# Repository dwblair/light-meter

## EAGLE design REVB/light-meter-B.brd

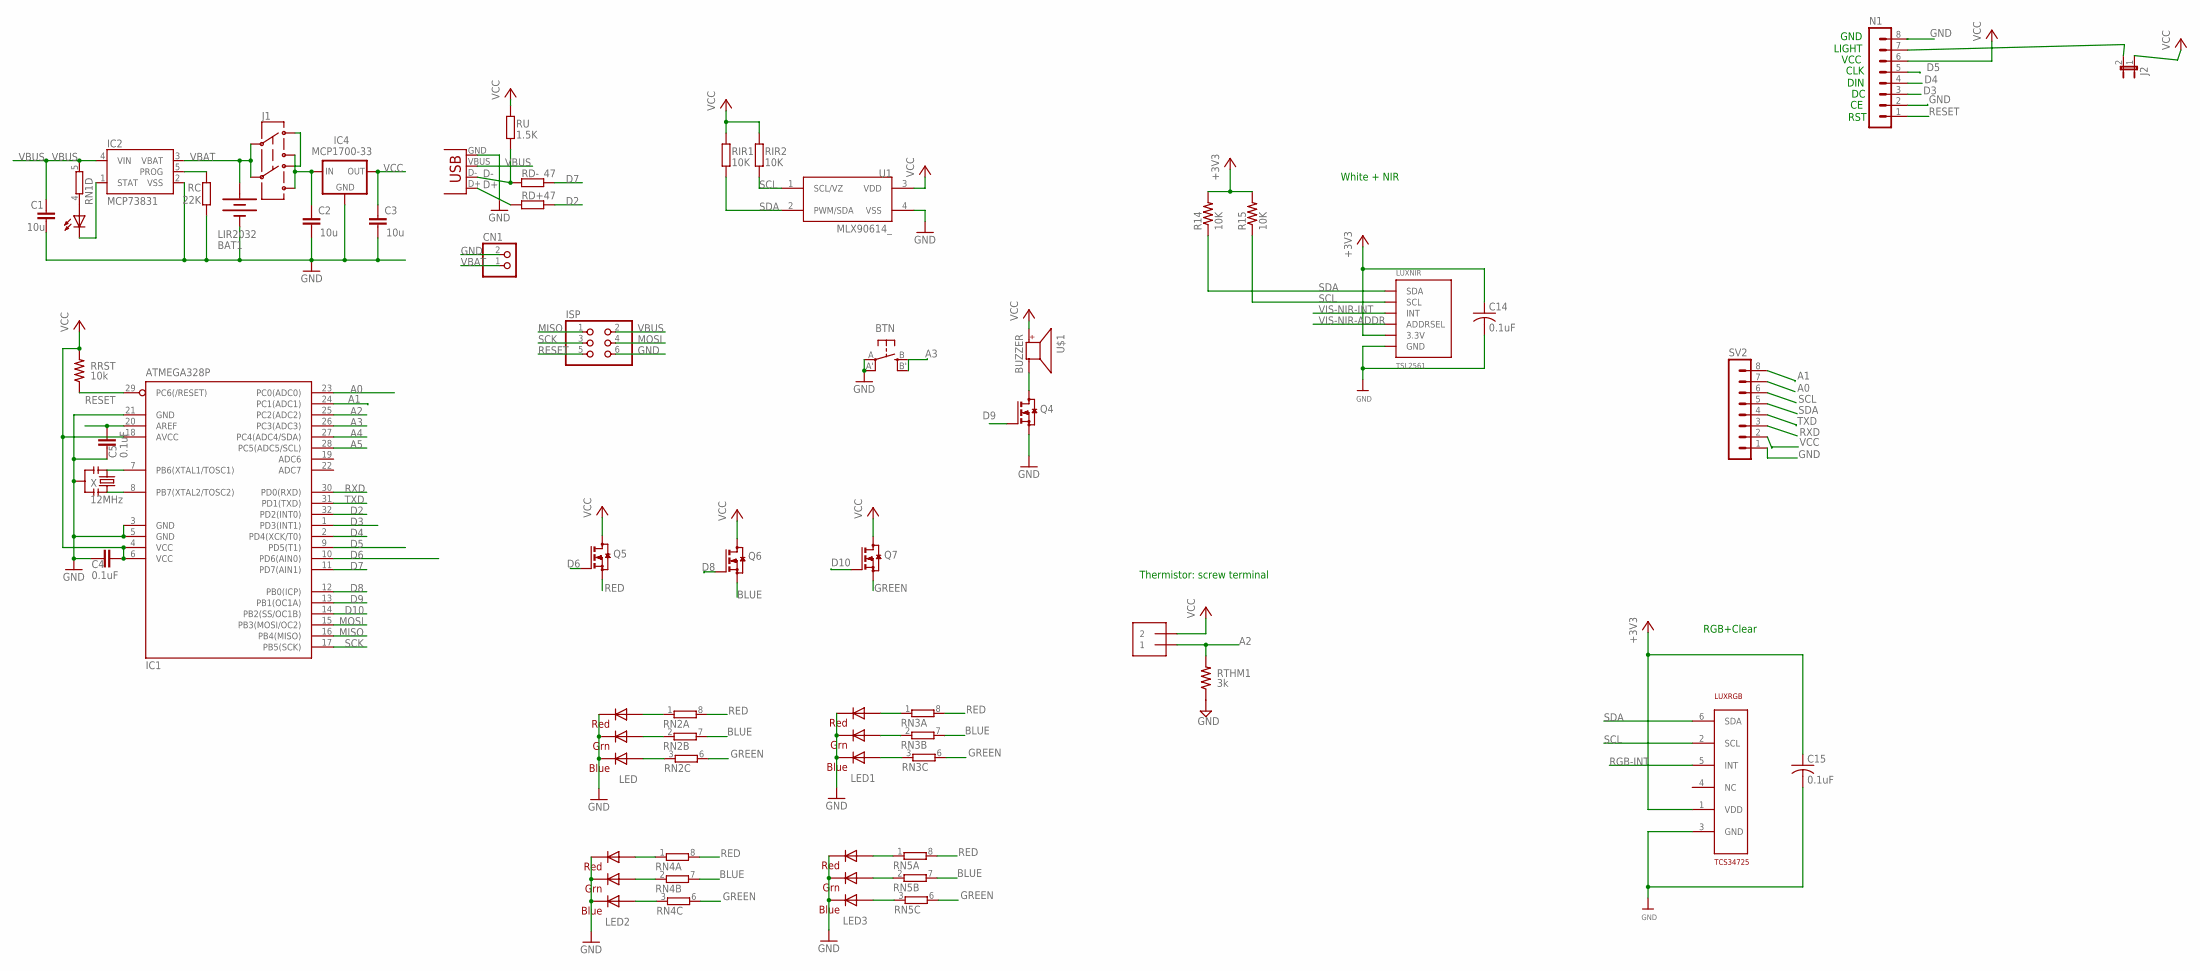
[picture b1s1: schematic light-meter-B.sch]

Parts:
BAT1: LIR2032; BATTCOM_20MM_PTH_SMT
BTN: EVQQ2; EVQ-Q2
C1, C2, C3: 10u; C0805
C4, C5, C14, C15: 0.1uF; C0805
CHG: 0805; CHIPLED_0805
CN1: JST_2PIN-SMT-RA; JST-PH-2-SMT-RA
IC1: ATMEGA328P; TQFP32-08
IC2: MCP73831; SOT23-5
IC4: MCP1700-33; SOT23
ISP: PINHD-2X3; 2X03
J1: AYZ0202
J2: JP1E; JP1
LED, LED1, LED2, LED3: RGBLED5050
LUXNIR: TSL2561; TSL2561_FN@1
LUXRGB: TCS34725; DFN-6
N1: MA08-1
Q4, Q5, Q6, Q7: BSS123; SOT23
R14, R15: 10K; R0805
RC: 22K; R0805
RD+: 47; R0805
RD-: 47; R0805
RIR1, RIR2: 10K; R0805
RN1, RN2, RN3, RN4, RN5: 4R-NEXB38V; EXB38V
RRST: 10k; R0805@1
RTHM1: 3k; R0805@1
RU: 1.5K; R0805
SV2: MA08-1
THM1: 1X2-3.5MM
U1: MLX90614_; TO-39
U$1: BUZZER; SMT-8585-BUZZER
X: 12MHz; RESONATOR-SMD
X1: USBSMD; USB-MINIB

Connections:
+3V3: C14.1, C15.1, LUXNIR.VDD (3.3V), LUXRGB.1 (VDD), R14.2, R15.2
A0: IC1.23 (PC0(ADC0)), SV2.7
A1: IC1.24 (PC1(ADC1)), SV2.8
A2: IC1.25 (PC2(ADC2)), RTHM1.2, THM1.1
A3: BTN.B (S), BTN.B' (S1), IC1.26 (PC3(ADC3))
A4: IC1.27 (PC4(ADC4/SDA))
A5: IC1.28 (PC5(ADC5/SCL))
AREF: C5.2, IC1.20 (AREF)
BLUE: Q6.2 (S), RN2.7 (2), RN3.7 (2), RN4.7 (2), RN5.7 (2)
D2: IC1.32 (PD2(INT0)), RD+.2
D3: IC1.1 (PD3(INT1)), N1.3
D4: IC1.2 (PD4(XCK/T0)), N1.4
D5: IC1.9 (PD5(T1)), N1.5
D6: IC1.10 (PD6(AIN0)), Q5.1 (G)
D7: IC1.11 (PD7(AIN1)), RD-.2
D8: IC1.12 (PB0(ICP)), Q6.1 (G)
D9: IC1.13 (PB1(OC1A)), Q4.1 (G)
D10: IC1.14 (PB2(SS/OC1B)), Q7.1 (G)
D+: RD+.1, X1.D+
D-: RD-.1, RU.1, X1.D-
GND: BAT1.P$1 (-), BTN.A, BTN.A' (P1), C1.2, C2.2, C3.2, C4.1, C5.1, C14.2, C15.2, CN1.2 (1), IC1.3 (GND), IC1.5 (GND), IC1.21 (GND), IC2.2 (VSS), IC4.1 (GND), ISP.6, LED.4 (BLUE_C), LED.5 (RED_C), LED.6 (GREEN_C), LED1.4 (BLUE_C), LED1.5 (RED_C), LED1.6 (GREEN_C), LED2.4 (BLUE_C), LED2.5 (RED_C), LED2.6 (GREEN_C), LED3.4 (BLUE_C), LED3.5 (RED_C), LED3.6 (GREEN_C), LUXNIR.VSS (GND), LUXRGB.3 (GND), N1.2, N1.8, Q4.2 (S), RC.1, RTHM1.1, SV2.1, U1.4 (VSS), X.2, X1.GND
GREEN: Q7.2 (S), RN2.6 (2), RN3.6 (2), RN4.6 (2), RN5.6 (2)
MISO: IC1.16 (PB4(MISO)), ISP.1
MOSI: IC1.15 (PB3(MOSI/OC2)), ISP.4
unnamed: J1.3 (1), J1.6 (4)
unnamed: IC1.7 (PB6(XTAL1/TOSC1)), X.1
unnamed: IC1.8 (PB7(XTAL2/TOSC2)), X.3
unnamed: LED.3 (BLUE_A), RN2.3 (1)
unnamed: CHG.C, IC2.1 (STAT)
unnamed: IC2.5 (PROG), RC.2
unnamed: Q4.3 (D), U$1.-
unnamed: J2.2, N1.7
unnamed: LED.1 (GREEN_A), RN2.2 (1)
unnamed: CHG.A, RN1.4 (1)
unnamed: LED.2 (RED_A), RN2.1
unnamed: LED1.3 (BLUE_A), RN3.3 (1)
unnamed: LED1.1 (GREEN_A), RN3.2 (1)
unnamed: LED1.2 (RED_A), RN3.1
unnamed: LED2.3 (BLUE_A), RN4.3 (1)
unnamed: LED2.1 (GREEN_A), RN4.2 (1)
unnamed: LED2.2 (RED_A), RN4.1
unnamed: LED3.3 (BLUE_A), RN5.3 (1)
unnamed: LED3.1 (GREEN_A), RN5.2 (1)
unnamed: LED3.2 (RED_A), RN5.1
RED: Q5.2 (S), RN2.8 (2), RN3.8 (2), RN4.8 (2), RN5.8 (2)
RESET: IC1.29 (PC6(/RESET)), ISP.5, N1.1, RRST.1
RGB-INT: LUXRGB.5 (INT)
RXD: IC1.30 (PD0(RXD)), SV2.3
SCK: IC1.17 (PB5(SCK)), ISP.3
SCL: LUXNIR.CLK (SCL), LUXRGB.2 (SCL), R15.1, RIR2.1, SV2.6, U1.1 (SCL/VZ)
SDA: LUXNIR.DATA (SDA), LUXRGB.6 (SDA), R14.1, RIR1.1, SV2.5, U1.2 (PWM/SDA)
TXD: IC1.31 (PD1(TXD)), SV2.4
VBAT: BAT1.P$2 (+), CN1.1 (2), IC2.3 (VBAT), J1.2, J1.5
VBUS: C1.1, IC2.4 (VIN), ISP.2, RN1.5 (2), X1.VBUS
VCC: C3.1, C4.2, IC1.4 (VCC), IC1.6 (VCC), IC1.18 (AVCC), IC4.2 (OUT), J2.1, N1.6, Q5.3 (D), Q6.3 (D), Q7.3 (D), RIR1.2, RIR2.2, RRST.2, RU.2, SV2.2, THM1.2, U1.3 (VDD), U$1.+
VDD: C2.1, IC4.3 (IN), J1.1 (3), J1.4 (6)
VIS-NIR-ADDR: LUXNIR.ADR (ADDRSEL)
VIS-NIR-INT: LUXNIR.INT

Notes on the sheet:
RGB+Clear
White + NIR
RST
DIN
CLK
VCC
LIGHT
GND
Thermistor: screw terminal

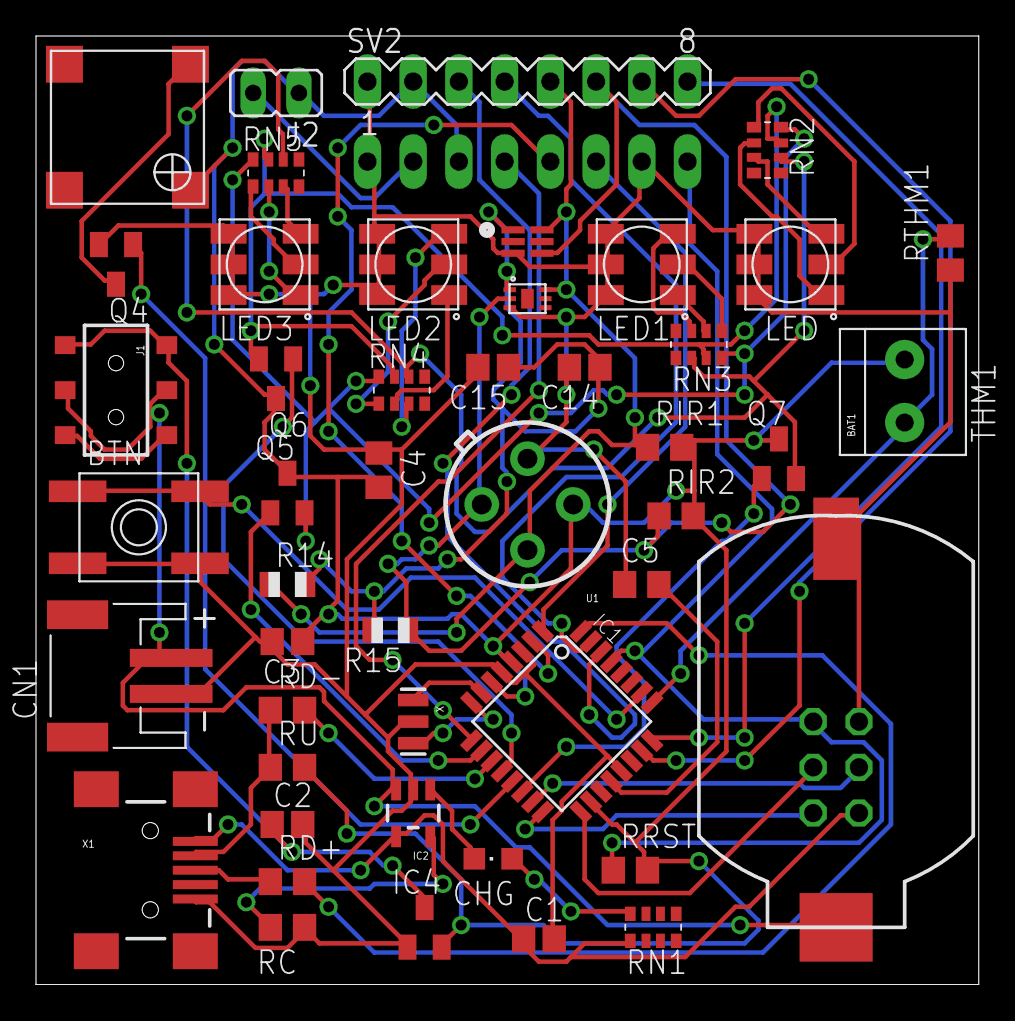
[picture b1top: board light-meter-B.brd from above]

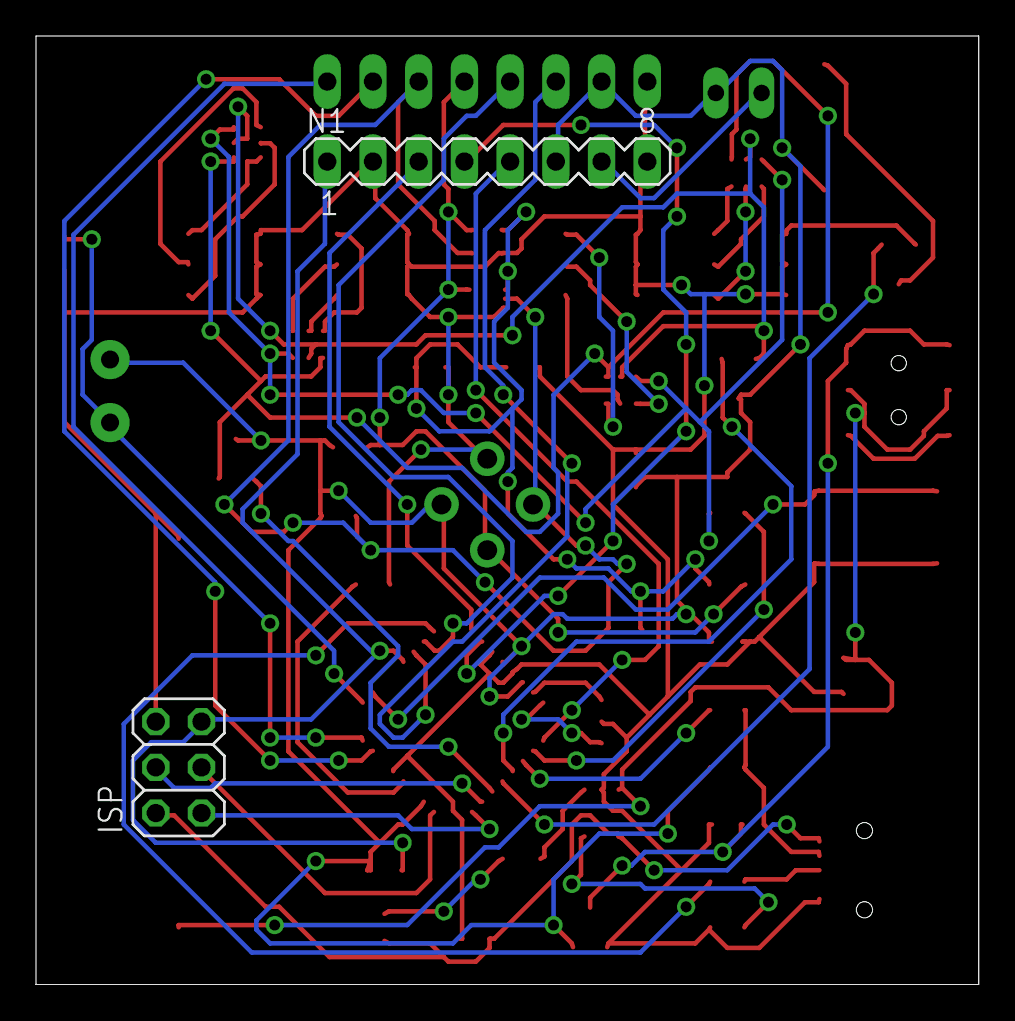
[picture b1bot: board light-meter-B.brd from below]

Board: 2 copper layers, 52.4 x 52.7 mm, 49 parts (2 on the bottom side), 53 nets.

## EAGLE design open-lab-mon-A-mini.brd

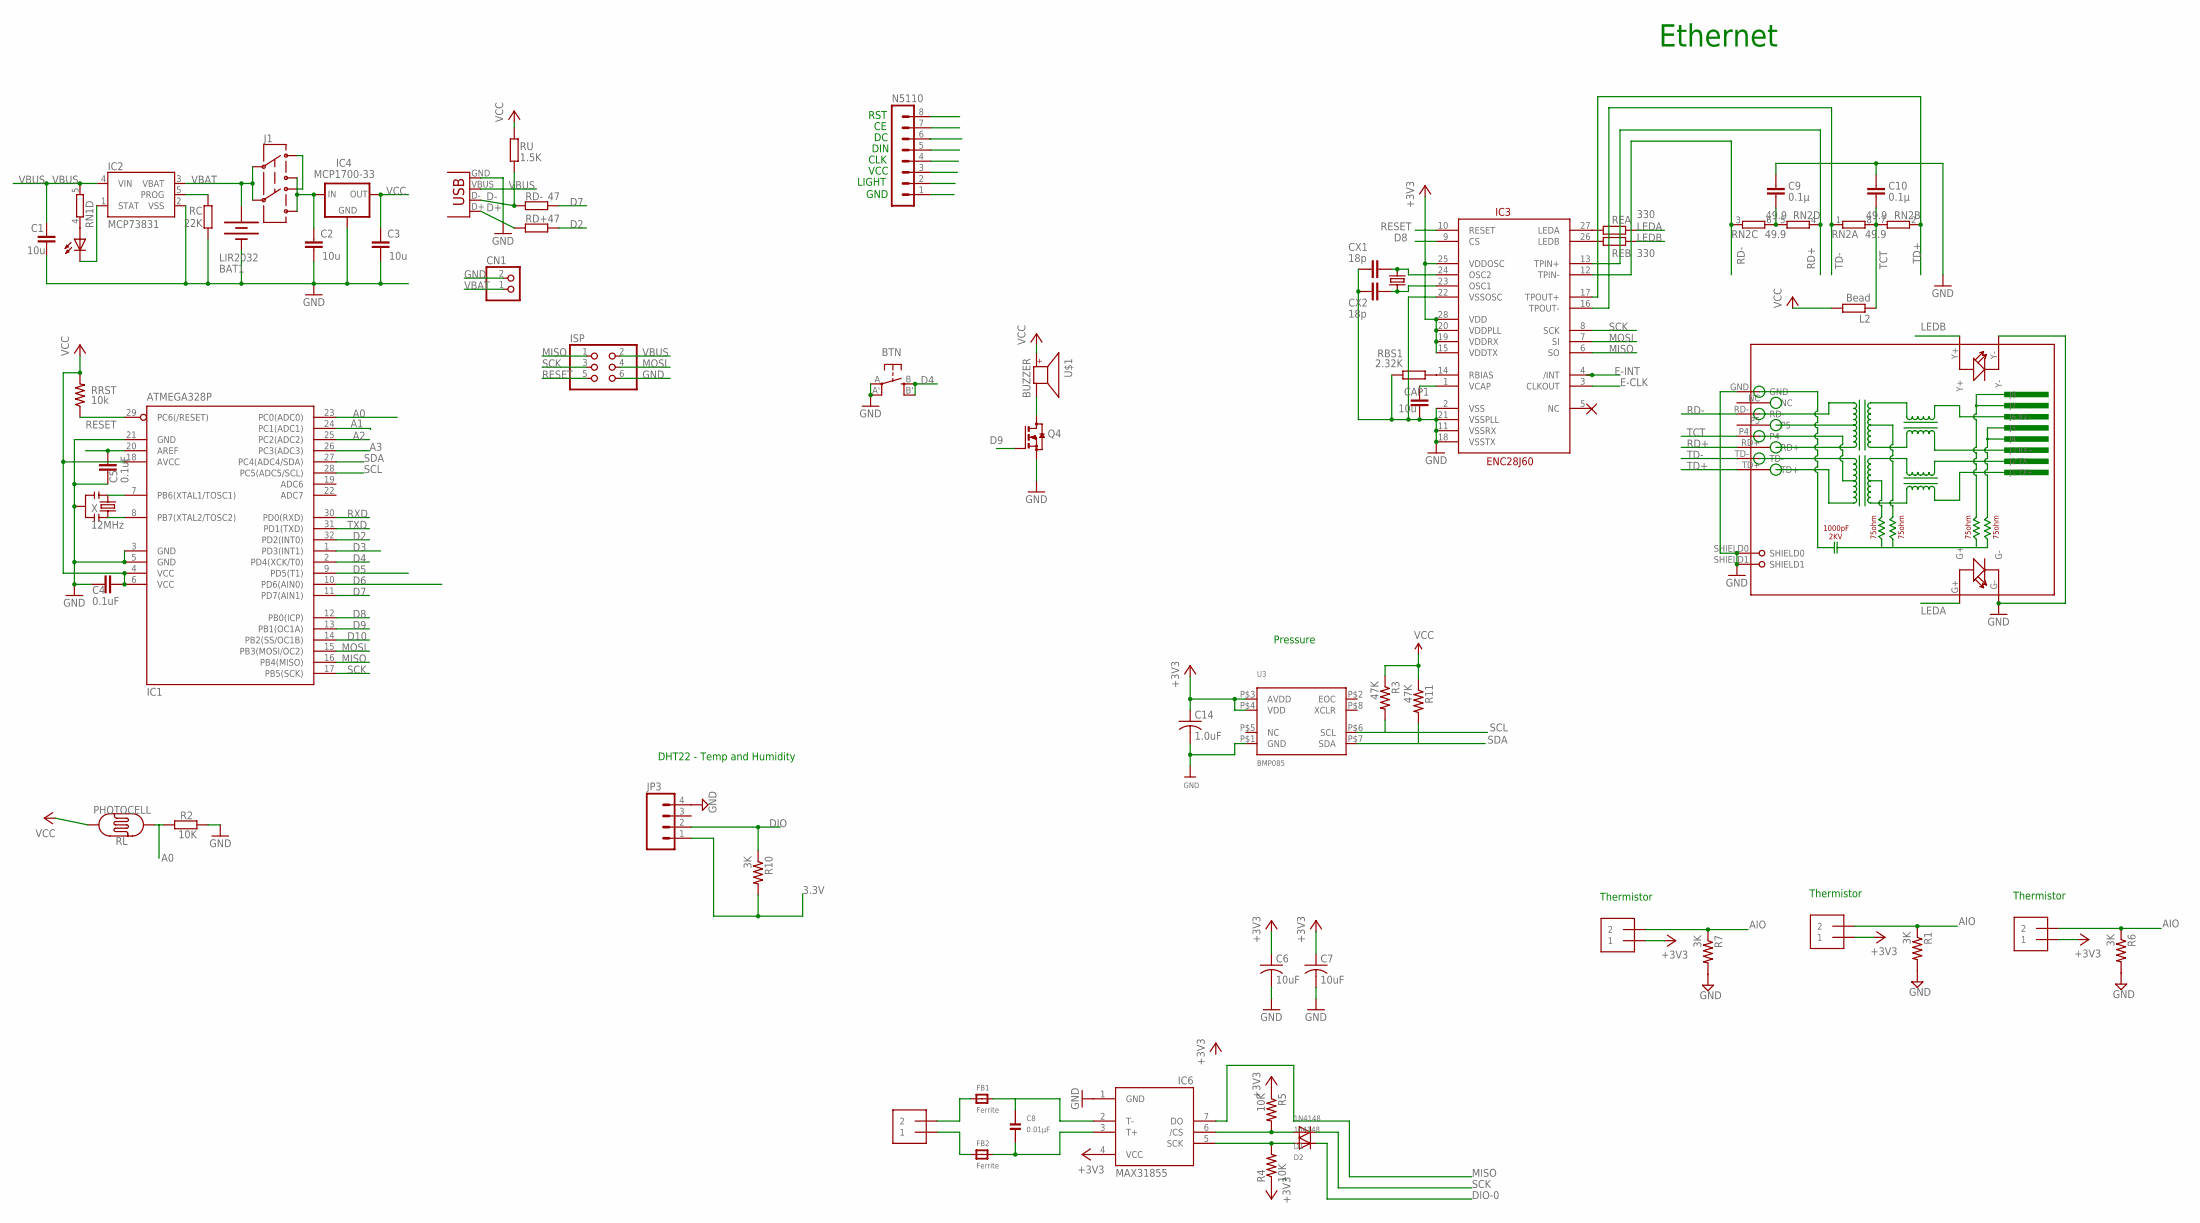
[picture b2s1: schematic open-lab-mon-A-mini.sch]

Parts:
BAT1: LIR2032; BATTCOM_20MM_PTH_SMT
BTN: EVQQ2; EVQ-Q2
C1, C2, C3: 10u; C0805
C4, C5: 0.1uF; C0805
C6, C7: 10uF; C0805K
C8: 0.01µF; _0805
C9, C10: 0.1µ; C0805
C14: 1.0uF; C0805
CAP1: 10u; C0805
CHG: 0805; CHIPLED_0805
CN1: JST_2PIN-SMT-RA; JST-PH-2-SMT-RA
CX1, CX2: 18p; C0805
D1: 1N4148; SOD-323F
D2: 1n4148; SOD-323F
FB1, FB2: Ferrite; _0805
IC1: ATMEGA328P; TQFP32-08
IC2: MCP73831; SOT23-5
IC3: ENC28J60; SOIC28WLONG
IC4: MCP1700-33; SOT23
IC6: MAX31855; SO08
ISP: PINHD-2X3; 2X03
J1: AYZ0202
J2, J3, J4, J5: 1X2-3.5MM
JP3: M04LOCK; 1X04_LOCK
L2: Bead; R0805
N5110: MA08-1
Q4: BSS123; SOT23
R1, R6, R7, R10: 3K; R0805
R2, R4, R5: 10K; R0805
R3, R11: 47K; R0805
RBS1: 2.32K; R0805
RC: 22K; R0805
RD+: 47; R0805
RD-: 47; R0805
REA: 330; R0805
REB: 330; R0805
RJ1: HR911105A
RL: PHOTOCELL
RN1: 4R-NEXB38V; EXB38V
RN2: 49.9; EXB38V
RRST: 10k; R0805@1
RU: 1.5K; R0805
U3: BMP085
U$1: BUZZER; SMT-8585-BUZZER
X: 12MHz; RESONATOR-SMD
X1: USBSMD; USB-MINIB
X2A: 25MHz; CRYSTAL-SMD-10.5X4.8-2PIN

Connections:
3.3V: JP3.1, R10.2
+3V3: C6.1, C7.1, C14.1, IC3.15 (VDDTX), IC3.19 (VDDRX), IC3.20 (VDDPLL), IC3.25 (VDDOSC), IC3.28 (VDD), IC6.4 (VCC), J3.1, J4.1, J5.1, R4.1, R5.1, U3.P$3 (AVDD), U3.P$4 (VDD)
A0: IC1.23 (PC0(ADC0)), R2.1, RL.1
A1: IC1.24 (PC1(ADC1))
A2: IC1.25 (PC2(ADC2))
A3: IC1.26 (PC3(ADC3))
AIO: J3.2, J4.2, J5.2, R1.1, R6.1, R7.1
AREF: C5.2, IC1.20 (AREF)
CS: D1.A, IC6.6 (/CS), R5.2
D2: IC1.32 (PD2(INT0)), RD+.2
D3: IC1.1 (PD3(INT1))
D4: BTN.B (S), BTN.B' (S1), IC1.2 (PD4(XCK/T0))
D5: IC1.9 (PD5(T1))
D6: IC1.10 (PD6(AIN0))
D7: IC1.11 (PD7(AIN1)), RD-.2
D8: IC1.12 (PB0(ICP)), IC3.9 (CS)
D9: IC1.13 (PB1(OC1A)), Q4.1 (G)
D10: IC1.14 (PB2(SS/OC1B))
D+: RD+.1, X1.D+
D-: RD-.1, RU.1, X1.D-
DIO: JP3.2, R10.1
DIO-0: D2.C
E-CLK: IC3.3 (CLKOUT)
E-INT: IC3.4 (/INT)
GND: BAT1.P$1 (-), BTN.A, BTN.A' (P1), C1.2, C2.2, C3.2, C4.1, C5.1, C6.2, C7.2, C9.1, C10.1, C14.2, CAP1.2, CN1.2 (1), CX1.2, CX2.2, IC1.3 (GND), IC1.5 (GND), IC1.21 (GND), IC2.2 (VSS), IC3.2 (VSS), IC3.11 (VSSRX), IC3.18 (VSSTX), IC3.21 (VSSPLL), IC3.22 (VSSOSC), IC4.1 (GND), IC6.1 (GND), ISP.6, JP3.4, Q4.2 (S), R1.2, R2.2, R6.2, R7.2, RBS1.1, RC.1, RJ1.G-, RJ1.GND, RJ1.SHIELD0, RJ1.SHIELD1, RJ1.Y-, U3.P$1 (GND), X.2, X1.GND
LEDA: REA.2, RJ1.G+
LEDB: REB.2, RJ1.Y+
MISO: IC1.16 (PB4(MISO)), IC3.6 (SO), IC6.7 (DO), ISP.1
MOSI: IC1.15 (PB3(MOSI/OC2)), IC3.7 (SI), ISP.4
unnamed: J1.3 (1), J1.6 (4)
unnamed: IC1.7 (PB6(XTAL1/TOSC1)), X.1
unnamed: IC1.8 (PB7(XTAL2/TOSC2)), X.3
unnamed: C9.2, RN2.5 (2), RN2.6 (2)
unnamed: CHG.C, IC2.1 (STAT)
unnamed: IC2.5 (PROG), RC.2
unnamed: Q4.3 (D), U$1.-
unnamed: FB1.1, J2.2
unnamed: C8.1, FB1.2, IC6.2 (T-)
unnamed: CHG.A, RN1.4 (1)
unnamed: FB2.1, J2.1
unnamed: C8.2, FB2.2, IC6.3 (T+)
unnamed: IC3.27 (LEDA), REA.1
unnamed: IC3.26 (LEDB), REB.1
unnamed: CAP1.1, IC3.1 (VCAP)
unnamed: IC3.14 (RBIAS), RBS1.2
unnamed: CX1.1, IC3.24 (OSC2), X2A.P$2 (2)
unnamed: CX2.1, IC3.23 (OSC1), X2A.P$1 (1)
RD+: IC3.13 (TPIN+), RJ1.RD+, RN2.4 (1)
RD-: IC3.12 (TPIN-), RJ1.RD-, RN2.3 (1)
RESET: IC1.29 (PC6(/RESET)), IC3.10 (RESET), ISP.5, RRST.1
RXD: IC1.30 (PD0(RXD))
SCK: D1.C, IC1.17 (PB5(SCK)), IC3.8 (SCK), ISP.3
SCK1: D2.A, IC6.5 (SCK), R4.2
SCL: IC1.28 (PC5(ADC5/SCL)), U3.P$6 (SCL)
SCL1: R3.2
SDA: IC1.27 (PC4(ADC4/SDA)), U3.P$7 (SDA)
SDA1: R11.2
TCT: C10.2, L2.1, RJ1.P4, RN2.7 (2), RN2.8 (2)
TD+: IC3.17 (TPOUT+), RJ1.TD+, RN2.2 (1)
TD-: IC3.16 (TPOUT-), RJ1.TD-, RN2.1
TXD: IC1.31 (PD1(TXD))
VBAT: BAT1.P$2 (+), CN1.1 (2), IC2.3 (VBAT), J1.2, J1.5
VBUS: C1.1, IC2.4 (VIN), ISP.2, RN1.5 (2), X1.VBUS
VCC: C3.1, C4.2, IC1.4 (VCC), IC1.6 (VCC), IC1.18 (AVCC), IC4.2 (OUT), L2.2, R3.1, R11.1, RL.2, RRST.2, RU.2, U$1.+
VDD: C2.1, IC4.3 (IN), J1.1 (3), J1.4 (6)

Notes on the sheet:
RST
DIN
CLK
VCC
LIGHT
GND
Ethernet
DHT22 - Temp and Humidity
Pressure
Thermistor

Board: 2 copper layers, 63 parts (0 on the bottom side), 51 nets, no tracks yet.

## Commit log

2014-04-05 initial layout
2014-04-06 tighter board

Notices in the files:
parts and their libraries:
microbuilder: This work is placed in the public domain, and may be freely used for commercial and non-commercial work with the following conditions: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
SparkFun-Connectors: Licensing: CC v3.0 Share-Alike You are welcome to use this library for commercial purposes.
